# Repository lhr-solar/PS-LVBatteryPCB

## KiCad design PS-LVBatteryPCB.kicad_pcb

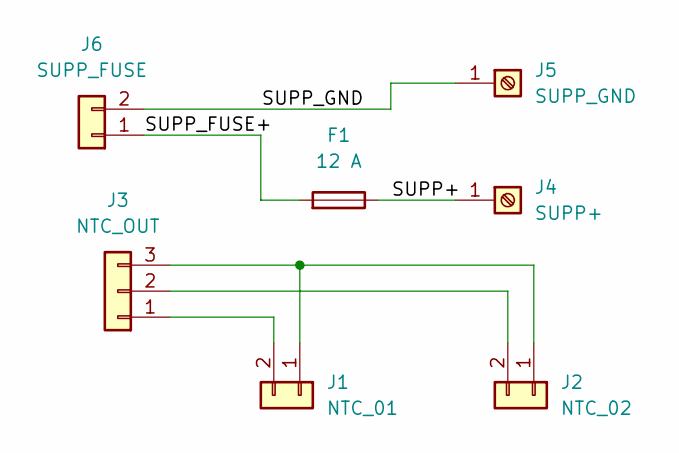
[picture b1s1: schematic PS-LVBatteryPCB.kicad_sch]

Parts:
F1: 12 A; Fuseholder_Blade_Mini_Keystone_3568
J1: NTC_01; Molex_Nano-Fit_105313-xx02_1x02_P2.50mm_Horizontal
J2: NTC_02; Molex_Nano-Fit_105313-xx02_1x02_P2.50mm_Horizontal
J3: NTC_OUT; Molex_Nano-Fit_105309-xx03_1x03_P2.50mm_Vertical
J4: SUPP+; KEYSTONE_8191-SEMS
J5: SUPP_GND; KEYSTONE_8191-SEMS
J6: SUPP_FUSE; AMASS_XT30UPB-M_1x02_P5.0mm_Vertical

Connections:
/SUPP+: F1.1, J4.1
/SUPP_FUSE+: F1.2, J6.1
/SUPP_GND: J5.1, J6.2
unnamed: J1.1, J2.1, J3.3
unnamed: J1.2, J3.1
unnamed: J2.2, J3.2

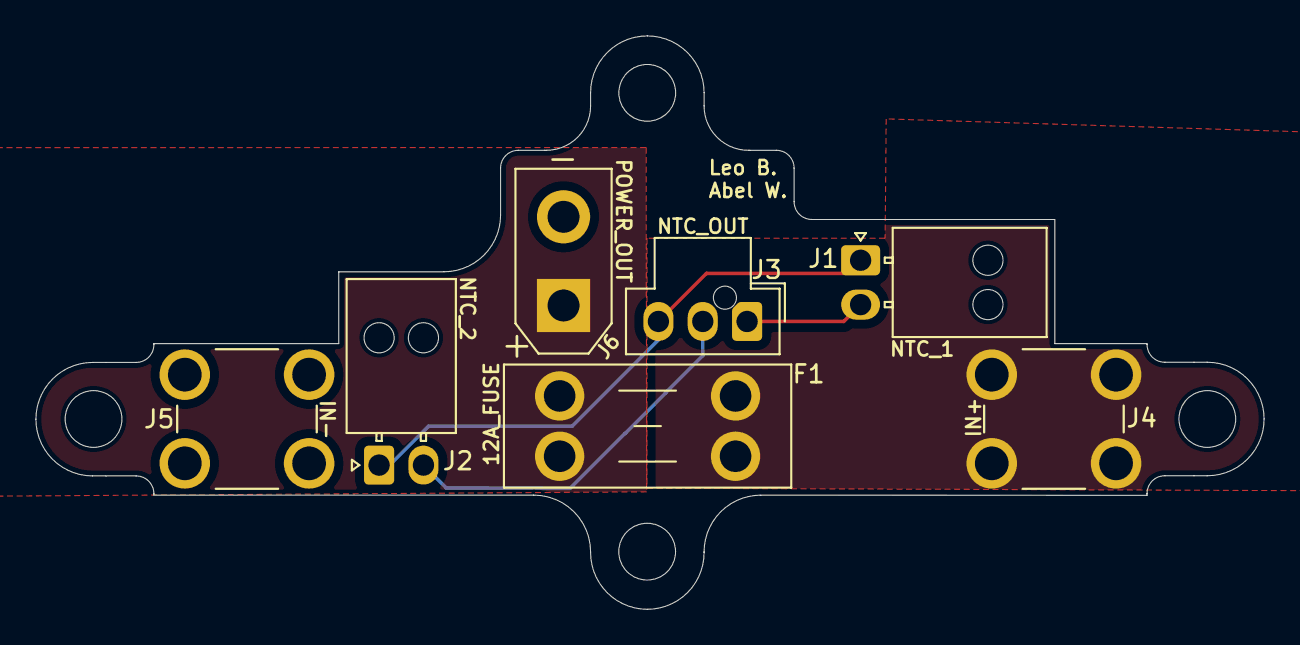
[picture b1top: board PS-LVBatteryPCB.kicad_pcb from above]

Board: 2 copper layers, 69.2 x 32.3 mm, 7 parts (0 on the bottom side), 6 nets.

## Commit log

2025-10-07 empty proj + submodule
2025-10-07 fp lib
2025-10-07 Rename gitignore.txt to .gitignore
2025-10-07 initial schem
2025-10-07 updated fps
2025-10-07 set-submodule branch
2025-10-08 added footprints/layout
2025-10-08 Added all fp's, added edge and planes, added traces, lots of errors
2025-10-09 reorganized pcb and changed up fp's
2025-10-09 reorganize and added SOME 3D models
2025-10-09 reorganized layout, gotta add planes
2025-10-10 revert
2025-10-10 thinner layout
2025-10-11 Specified some silkscreen labels + attribution
2025-10-12 centered top mount, touched up ss
2025-10-14 redid layout for optimal terminal shape
2025-10-14 moved mounting holes
2025-10-15 ss fix, trace fix
2025-10-15 increased plane thickness for GND
2025-10-15 Add Gerber folder for RevA
2025-10-24 BOM + CPL added
2025-10-24 BOM added
